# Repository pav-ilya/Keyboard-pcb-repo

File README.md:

Zvezda is a 40% winkeyless through-hole keyboard.

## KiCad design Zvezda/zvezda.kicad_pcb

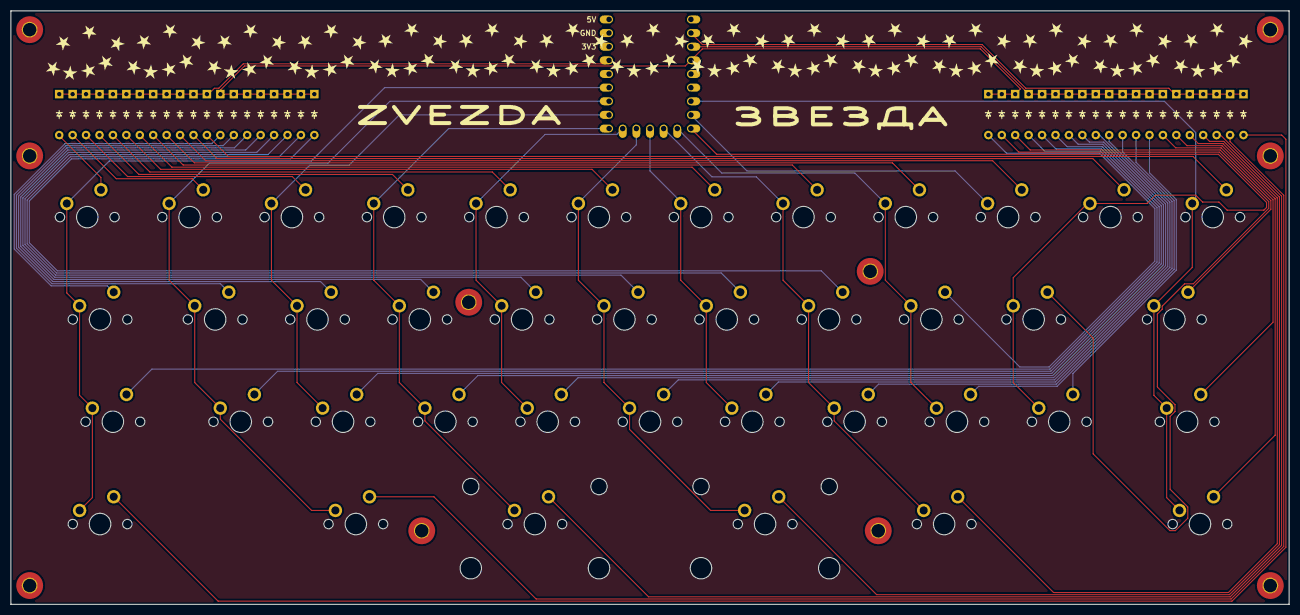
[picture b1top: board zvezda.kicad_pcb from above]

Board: 2 copper layers, 238.0 x 110.5 mm, 91 parts (0 on the bottom side), 56 nets.

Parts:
D1, D2, D3, D4, D5, D6, D7, D8, D9, D10, D11, D12, D13, D14, D15, D16, D17, D18, D19, D20, D21, D22, D23, D24, D25, D26, D27, D28, D29, D30, D31, D32, D33, D34, D35, D36, D37, D38, D39, D40: Diode_DO-35
H1, H2, H3, H4, H4#2, H4#3, H4#4, H4#5, H5, H6: MountingHole_2.5mm_Pad_TopBottom
S1, S2, S3, S4, S5, S6, S7, S8, S9, S10, S11, S12, S14, S15, S16, S17, S18, S19, S20, S21, S22, S25, S26, S27, S28, S29, S30, S31, S32, S33: MX_PCB_1.00u
S13, S35, S36, S39, S40: MX_PCB_1.25u
S23: MX_PCB_1.75u
S24, S34: MX_PCB_1.50u
S37, S38: MX_PCB_2.25u
U1: RP2040_Zero

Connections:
/C0: S1.1, S13.1, S24.1, S35.1, U1.18 (27)
/C1: S2.1, S14.1, S25.1, S36.1, U1.17 (26)
/C2: S3.1, S15.1, S26.1, U1.16 (15)
/C3: S4.1, S16.1, S27.1, S37.1, U1.15 (14)
/C4: S5.1, S17.1, S28.1, U1.14 (13)
/C5: S6.1, S18.1, S29.1, S38.1, U1.13 (12)
/C6: S7.1, S19.1, S30.1, U1.12 (11)
/C7: S8.1, S20.1, S31.1, S39.1, U1.11 (10)
/C8: S9.1, S21.1, S32.1, U1.10 (9)
/C9: S10.1, U1.8 (7)
/C10: S11.1, S22.1, S33.1, U1.9 (8)
/C11: S12.1, S23.1, S34.1, S40.1, U1.7 (6)
/R0: D35.1 (K), D36.1 (K), D37.1 (K), D38.1 (K), D39.1 (K), D40.1 (K), U1.2 (1)
/R1: D22.1 (K), D25.1 (K), D26.1 (K), D27.1 (K), D28.1 (K), D29.1 (K), D30.1 (K), D31.1 (K), D32.1 (K), D33.1 (K), D34.1 (K), U1.3 (2)
/R2: D13.1 (K), D14.1 (K), D15.1 (K), D16.1 (K), D17.1 (K), D18.1 (K), D19.1 (K), D20.1 (K), D21.1 (K), D23.1 (K), D24.1 (K), U1.4 (3)
/R3: D1.1 (K), D2.1 (K), D3.1 (K), D4.1 (K), D5.1 (K), D6.1 (K), D7.1 (K), D8.1 (K), D9.1 (K), D10.1 (K), D11.1 (K), D12.1 (K), U1.20 (29)
unnamed: D1.2 (A), S1.2
unnamed: D2.2 (A), S2.2
unnamed: D3.2 (A), S3.2
unnamed: D4.2 (A), S4.2
unnamed: D5.2 (A), S5.2
unnamed: D6.2 (A), S6.2
unnamed: D7.2 (A), S7.2
unnamed: D8.2 (A), S8.2
unnamed: D9.2 (A), S9.2
unnamed: D10.2 (A), S10.2
unnamed: D11.2 (A), S11.2
unnamed: D12.2 (A), S12.2
unnamed: D13.2 (A), S13.2
unnamed: D14.2 (A), S14.2
unnamed: D15.2 (A), S15.2
unnamed: D16.2 (A), S16.2
unnamed: D17.2 (A), S17.2
unnamed: D18.2 (A), S18.2
unnamed: D19.2 (A), S19.2
unnamed: D20.2 (A), S20.2
unnamed: D21.2 (A), S21.2
unnamed: D22.2 (A), S24.2
unnamed: D23.2 (A), S22.2
unnamed: D24.2 (A), S23.2
unnamed: D25.2 (A), S25.2
unnamed: D26.2 (A), S26.2
unnamed: D27.2 (A), S27.2
unnamed: D28.2 (A), S28.2
unnamed: D29.2 (A), S29.2
unnamed: D30.2 (A), S30.2
unnamed: D31.2 (A), S31.2
unnamed: D32.2 (A), S32.2
unnamed: D33.2 (A), S33.2
unnamed: D34.2 (A), S34.2
unnamed: D35.2 (A), S35.2
unnamed: D36.2 (A), S36.2
unnamed: D37.2 (A), S37.2
unnamed: D38.2 (A), S38.2
unnamed: D39.2 (A), S39.2
unnamed: D40.2 (A), S40.2

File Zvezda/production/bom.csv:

Designator,Footprint,Quantity,Value,LCSC Part #
"D1, D10, D11, D12, D13, D14, D15, D16, D17, D18, D19, D2, D20, D21, D22, D23, D24, D25, D26, D27, D28, D29, D3, D30, D31, D32, D33, D34, D35, D36, D37, D38, D39, D4, D40, D5, D6, D7, D8, D9",Diode_DO-35,40,~,
"H1, H2, H3, H4_5, H5, H6",MountingHole_2.5mm_Pad_TopBottom,6,~,
"S1, S10, S11, S12, S14, S15, S16, S17, S18, S19, S2, S20, S21, S22, S25, S26, S27, S28, S29, S3, S30, S31, S32, S33, S4, S5, S6, S7, S8, S9",MX_PCB_1.00u,30,~,
"S13, S35, S36, S39, S40",MX_PCB_1.25u,5,~,
S23,MX_PCB_1.75u,1,~,
"S24, S34",MX_PCB_1.50u,2,~,
"S37, S38",MX_PCB_2.25u,2,~,
U1,RP2040_Zero,1,RP2040_Zero,
